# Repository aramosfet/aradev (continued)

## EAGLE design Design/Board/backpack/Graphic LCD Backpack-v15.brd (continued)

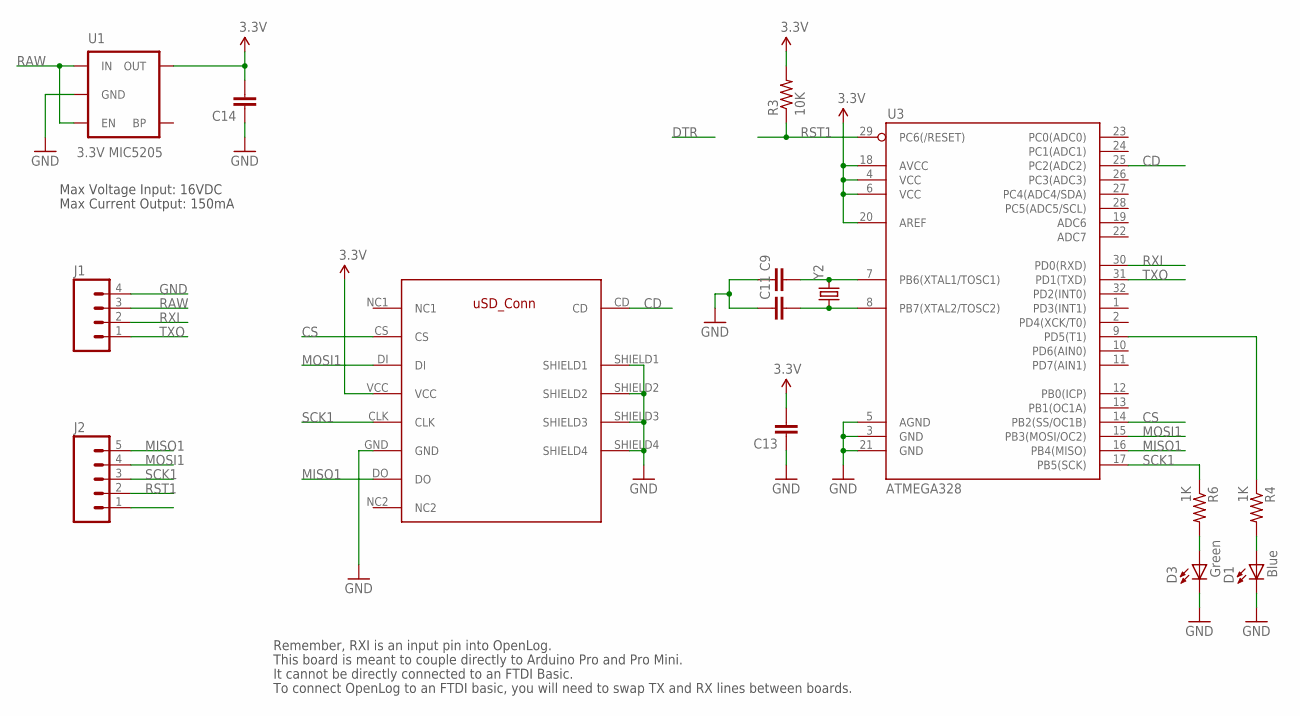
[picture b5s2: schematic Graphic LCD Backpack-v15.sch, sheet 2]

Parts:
C9, C11, C13, C14: CAP1206; 1206
D1: Blue; LED-1206
D3: Green; LED-1206
J1: M04PTH; 1X04
J2: M05PTH; 1X05
R3: 10K; 0805
R4, R6: 1K; 0805
U1: 3.3V MIC5205; SOT23-5
U3: ATMEGA328; TQFP32-08
U$3: USD_CONN
Y2: CRYSTALHC49US; HC49US

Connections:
3.3V: C13.2, C14.2, R3.2, U1.5 (OUT), U3.4 (VCC), U3.6 (VCC), U3.18 (AVCC), U3.20 (AREF), U$3.VCC
CD: U3.25 (PC2(ADC2)), U$3.CD
CS: U3.14 (PB2(SS/OC1B)), U$3.CS
GND: C9.1, C11.1, C13.1, C14.1, D1.C, D3.C, J1.4, J2.1, U1.2 (GND), U3.3 (GND), U3.5 (AGND), U3.21 (GND), U$3.GND, U$3.SHIELD1, U$3.SHIELD2, U$3.SHIELD3, U$3.SHIELD4; also elsewhere on the board
MISO1: J2.5, U3.16 (PB4(MISO)), U$3.DO
MOSI1: J2.4, U3.15 (PB3(MOSI/OC2)), U$3.DI
unnamed: D1.A, R4.2
unnamed: D3.A, R6.2
unnamed: R4.1, U3.9 (PD5(T1))
unnamed: C9.2, U3.7 (PB6(XTAL1/TOSC1)), Y2.2
unnamed: C11.2, U3.8 (PB7(XTAL2/TOSC2)), Y2.1
RAW: J1.3, U1.1 (IN), U1.3 (EN)
RST1: J2.2, R3.1, U3.29 (PC6(/RESET))
RXI: J1.2, U3.30 (PD0(RXD))
SCK1: J2.3, R6.1, U3.17 (PB5(SCK)), U$3.CLK
TXO: J1.1, U3.31 (PD1(TXD))

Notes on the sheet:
Max Voltage Input: 16VDC
Max Current Output: 150mA
Remember, RXI is an input pin into OpenLog.
This board is meant to couple directly to Arduino Pro and Pro Mini.
It cannot be directly connected to an FTDI Basic.
To connect OpenLog to an FTDI basic, you will need to swap TX and RX lines between boards.

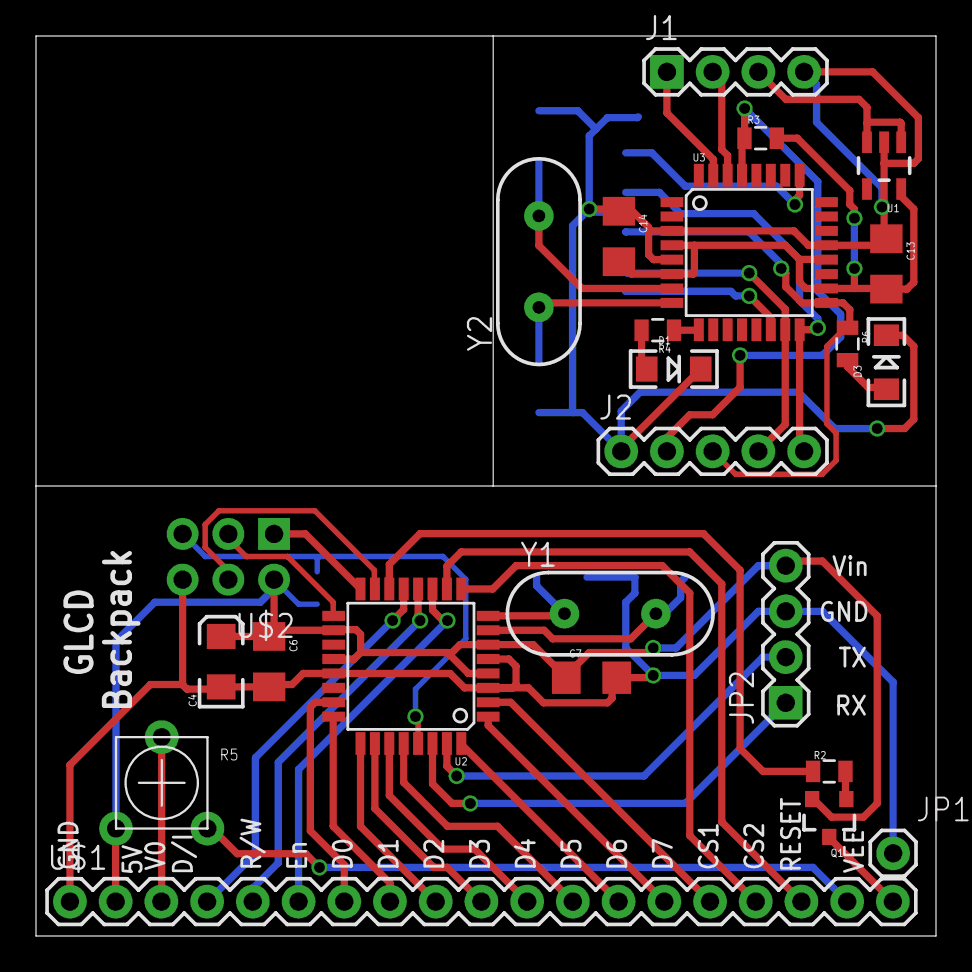
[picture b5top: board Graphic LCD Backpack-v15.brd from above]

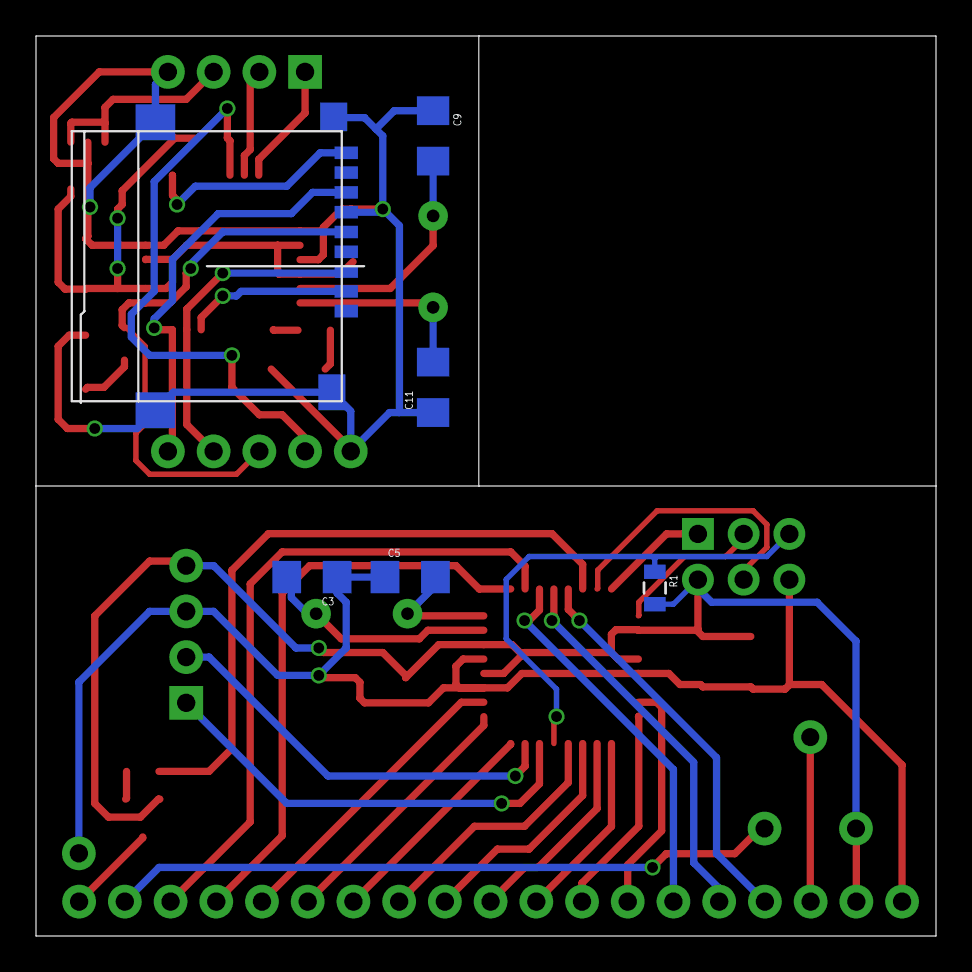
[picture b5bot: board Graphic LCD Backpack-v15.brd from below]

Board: 2 copper layers, 50.0 x 50.0 mm, 30 parts (6 on the bottom side), 44 nets.

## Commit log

2015-04-26 :circus_tent: Added .gitattributes
2015-04-26 AC Monitor Rev1
2016-02-27 Batch E added
